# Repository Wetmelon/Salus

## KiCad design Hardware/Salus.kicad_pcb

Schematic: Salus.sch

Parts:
C1, C2, C6, C7, C8, C13: 10uF; C_0805
C3, C4, C5: .01uF; C_0805
C9, C10, C14: 22uF; C_0805
C11, C12: 22pF; C_0805
CON1: MicroSD_Card; MicroSD_TF001B
D1: Led_Small; LED-0805
D2: LED; LED-0805
D3: D_Schottky; SMA_Standard
P1, P3: CONN_01X08; TerminalBlock_Pheonix_PT-3.5mm_8pol
P2: CONN_01X04; DF13-4
P4, P5, P6, P7: CONN_01X03; Pin_Header_Straight_1x03
Q1: Q_NMOS_GDS; SOT-23_Handsoldering
R1, R2, R3, R20: 10k; R_0805
R4, R5: 2.2k; R_0805
R6, R7, R8: 220R; R_0805
R9, R15: R; R_0805
R10, R11, R12: 1K; R_0805
R13: 40.2K; R_0805
R14, R16, R17, R18: 10K; R_0805
R19: 1k; R_0805
U1: ADXL377; QFP_16
U2: MS5607
U3: S25FL127SAMBFI101; SOIC-8-N
U4: FGMMOPA6H; FGPMMOPA6H
U5: uFL; U.FL-CON
U6: BUZZER; CT-1205C-SMT
U7, U8, U9: TCMT1103; SOIC-4
U10: TXB0104PWR; TSSOP-14
U11: Teensy_3.2; Teensy_3.2+4
U12, U13, U14: BTS6133D; TO-252-5
U15: BNO055; LGA28_5832
U16: AP1117; SOT-223
Y1: 32.768kHz; SOJ-4

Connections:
+3V3: C1.1, C2.1, C6.1, C7.1, C9.2, CON1.4 (VDD), R2.2, R3.1, R4.1, R5.1, R9.1, R15.1, U1.14 (VS), U1.15 (VS), U2.1 (VDD), U2.2 (PS), U2.4 (CSB), U2.5 (CSB), U3.5, U4.1 (VCC), U10.1 (VCCA), U11.26 (3.3V), U11.30 (3.3V), U15.3 (VDD), U15.28 (VDDIO)
+5V: C8.1, P3.2, P4.2, P5.2, P6.2, P7.2, U10.14 (VCCB)
+12V: P1.8, U12.3 (VBB), U13.3 (VBB), U14.3 (VBB)
/3VSERVO1: U10.2 (A1), U11.22 ((PWM)A6)
/3VSERVO2: U10.3 (A2), U11.23 ((PWM)A7)
/3VSERVO3: U10.4 (A3), U11.24 ((TOUCH/PWM)A8)
/3VSERVO4: U10.5 (A4), U11.25 ((TOUCH/PWM)A9)
/200GX: C5.1, U1.5 (XOUT), U11.16 (A0)
/200GY: C4.1, U1.4 (YOUT), U11.17 ((TOUCH)A1)
/200GZ: C3.1, U1.16 (ZOUT), U11.18 ((TOUCH)A2)
/BNO_INT: U11.8 ((PWM)6), U15.14 (INT)
/BNO_RES: R15.2, U11.9 ((RX3)7), U15.11 (RESET)
/BUZZER: Q1.1 (G), U11.4 (2)
/DEP0: R6.2, U11.7 ((PWM)5)
/DEP0-OUT: P1.6, U12.1 (OUT), U12.5 (OUT)
/DEP0_TRIG: U7.4, U12.2 (IN)
/DEP1: R7.2, U11.6 ((PWM/CANRX)4)
/DEP1-OUT: P1.4, U13.1 (OUT), U13.5 (OUT)
/DEP1_TRIG: U8.4, U13.2 (IN)
/DEP2: R8.2, U11.5 ((PWM/CANTX)3)
/DEP2-OUT: P1.2, U14.1 (OUT), U14.5 (OUT)
/DEP2_TRIG: U9.4, U14.2 (IN)
/FLASH_CS: U3.1, U11.10 ((TX3)8)
/FLASH_HOLD: R3.2, U3.6
/FLASH_WP: U3.3
/GPS_RX: U4.10 (RX), U11.11 ((PWM/RX2)9)
/GPS_TX: U4.9 (TX), U11.12 ((PWM/CS/TX2)10)
/MISO: CON1.7 (DAT0/DO), U3.2, U11.14 ((DIN/MISO)12)
/MOSI: CON1.3 (CMD/DI), U3.8, U11.13 ((DOUT/MOSI)11)
/SCK: CON1.5 (CLK/SCLK), U3.7, U11.15 ((SCK/LED)13)
/SCL: R5.2, U2.8 (SCLK), U11.21 ((TOUCH/SCL0)A5), U15.19 (SCL/RX/COM1)
/SDA: R4.2, U2.7 (SDI/SDA), U11.20 ((TOUCH/SDA0)A4), U15.20 (SDA/TX/COM0)
/SD_CS: CON1.2 (CS/DAT3), U11.19 ((TOUCH)A3)
/SERVO1: P4.1, U10.13 (B1)
/SERVO2: P5.1, U10.12 (B2)
/SERVO3: P6.1, U10.11 (B3)
/SERVO4: P7.1, U10.10 (B4)
/TEL_RX: P2.2, U11.2 ((RX1/TOUCH)0)
/TEL_TX: P2.3, U11.3 ((TX1/TOUCH)1)
GND: C1.2, C2.2, C3.2, C4.2, C5.2, C6.2, C7.2, C8.2, C9.1, C10.1, C11.1, C12.1, C13.2, C14.2, CON1.6 (VSS), D1.1 (K), P2.4, P3.1, P3.3, P3.5, P4.3, P5.3, P6.3, P7.3, Q1.3 (S), R14.1, R16.2, R17.2, R18.2, R19.2, R20.2, U1.1 (GND), U1.3 (GND), U1.6 (GND), U1.7 (GND), U2.3 (GND), U3.4, U4.3 (GND), U4.8 (GND), U4.12 (GND), U4.19 (GND), U5.2, U7.2, U8.2, U9.2, U10.7 (GND), U11.1 (GND), U11.27 (AGND), U11.31 (GND), U15.2 (GND), U15.10 (GNDIO), U15.15 (GNDIO), U15.16 (GNDIO), U15.18 (GNDI/COM2), U15.25 (GNDIO), U16.1 (GND/ADJ)
GNDPWR: P1.1, P1.3, P1.5, P1.7, R10.2, R11.2, R12.2, U7.3, U8.3, U9.3
unnamed: C10.2, U15.9 (CAP)
unnamed: C11.2, U15.27 (XIN32), Y1.1
unnamed: C12.2, U15.26 (XOUT32), Y1.4 (2)
unnamed: D1.2 (A), R1.1
unnamed: D2.1 (K), D3.2 (A), P3.4, P3.8, R20.1
unnamed: D2.2 (A), R19.1
unnamed: P3.6, P3.7
unnamed: Q1.2 (D), U6.2
unnamed: R1.2, U4.5 (3D-FIX)
unnamed: R2.1, U4.2 (RESET)
unnamed: R6.1, U7.1
unnamed: R7.1, U8.1
unnamed: R8.1, U9.1
unnamed: R9.2, U10.8 (OE)
unnamed: R10.1, U12.4 (IS)
unnamed: R11.1, U13.4 (IS)
unnamed: R12.1, U14.4 (IS)
unnamed: R13.1, R14.2, U11.33 ((DAC)A14)
unnamed: R16.1, U15.17 (ADR/GNDIO/COM3)
unnamed: R17.1, U15.6 (PS0)
unnamed: R18.1, U15.5 (PS1)
unnamed: U4.11 (EX_ANT), U5.1
VDD: C14.1, P2.1, U6.1 (+), U11.28 (VIN), U16.2 (VO)
VPP: C13.1, D3.1 (K), R13.2, U16.3 (VI)

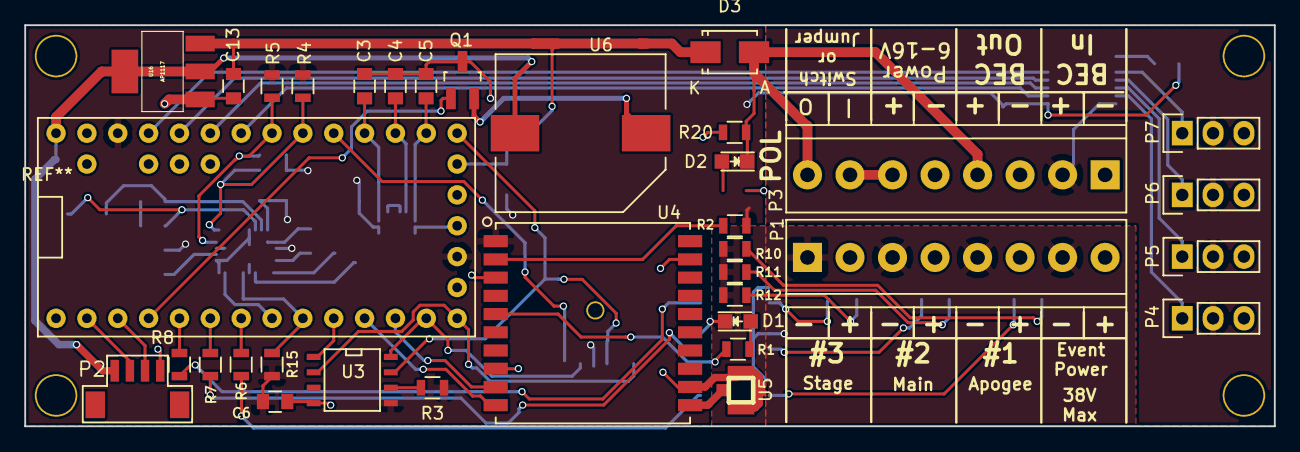
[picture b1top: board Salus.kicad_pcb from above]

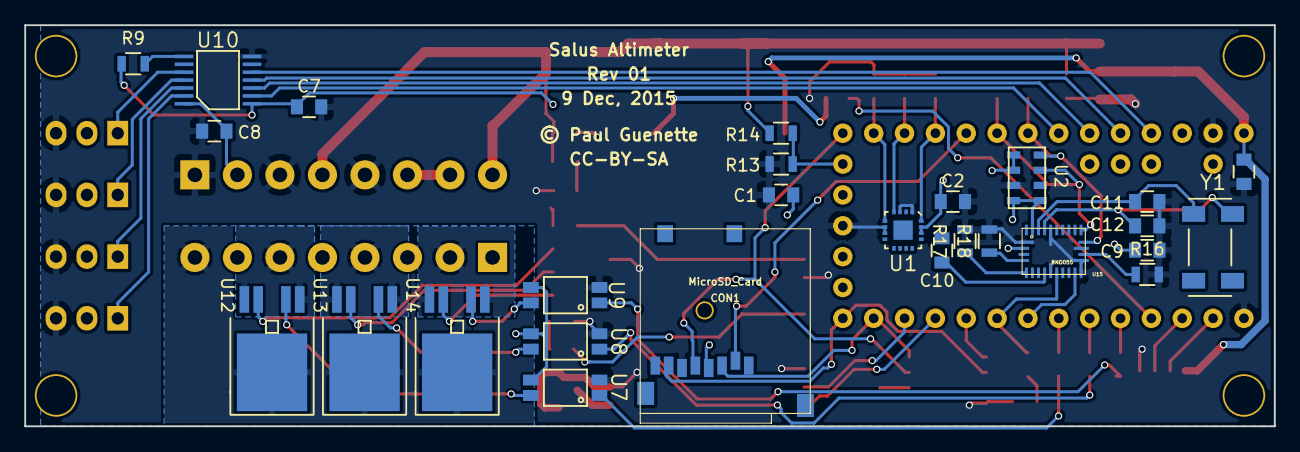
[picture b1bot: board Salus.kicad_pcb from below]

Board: 2 copper layers, 102.9 x 33.0 mm, 62 parts (27 on the bottom side), 63 nets.

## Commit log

2016-04-07 Salus project Init
2016-05-11 Large # of changes
2016-05-11 osr, accel changes
2016-05-12 Increase logging time to 1 hour
2016-05-25 Better Data Logging
2016-09-05 Speed up Serial comms, BNO has no ext. crystal
2016-09-06 Add Accel and Gyro events for BNO055
2016-09-08 Clear old code, add profiling code
2016-09-08 Add pinMode and default values for all connected pins
2016-09-08 Better barometer setup, debugging
2016-09-08 Return Baro to 200hz
2016-09-08 Remove Analog pin modes
2016-09-19 Tweaks to program flow
2016-11-02 Launch Detection
2016-11-02 Fix merge errors
2016-11-02 Update repo for sharing
2016-11-02 Add a non-blocking beep every 10 seconds
2016-11-06 Fix trigger orientation, short beeps during flight
2016-11-06 Fix logging file size (60 minutes)
2016-11-06 Reset "ground" altitude at liftoff
2016-11-14 Add Hardware to repo
2016-11-14 Add libraries folder
2016-11-14 Remove .lib from gitignore
2016-11-14 Move Wetmelon lib into folder, point schematic at it.
2016-11-27 Add PDFs
2017-03-23 Minor debug change
2017-03-23 Remove Libraries from Master
2017-03-23 Add Libs to Lib_Inc
2017-03-25 Replace the unpacking script with the correct one
2017-11-16 Include all required libraries
2017-11-16 Add 115200 baud option
2017-11-16 Change sensor ID to force re-calibration
2017-11-16 Remove Adafruit_GPS temporarily
2017-11-16 Add Adafruit_GPS again
2017-11-16 Speed up GPS communication to 115200 baud
2017-11-16 Remove submodules... again.
2017-11-16 Revert "Speed up GPS communication to 115200 baud"
    This reverts commit 62add5c53efce33f091733036830cb9ddf044977.
2017-11-16 re-add the missing libraries

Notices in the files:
Hardware/Salus.kicad_pcb:
CC-BY-SA
© Paul Guenette
